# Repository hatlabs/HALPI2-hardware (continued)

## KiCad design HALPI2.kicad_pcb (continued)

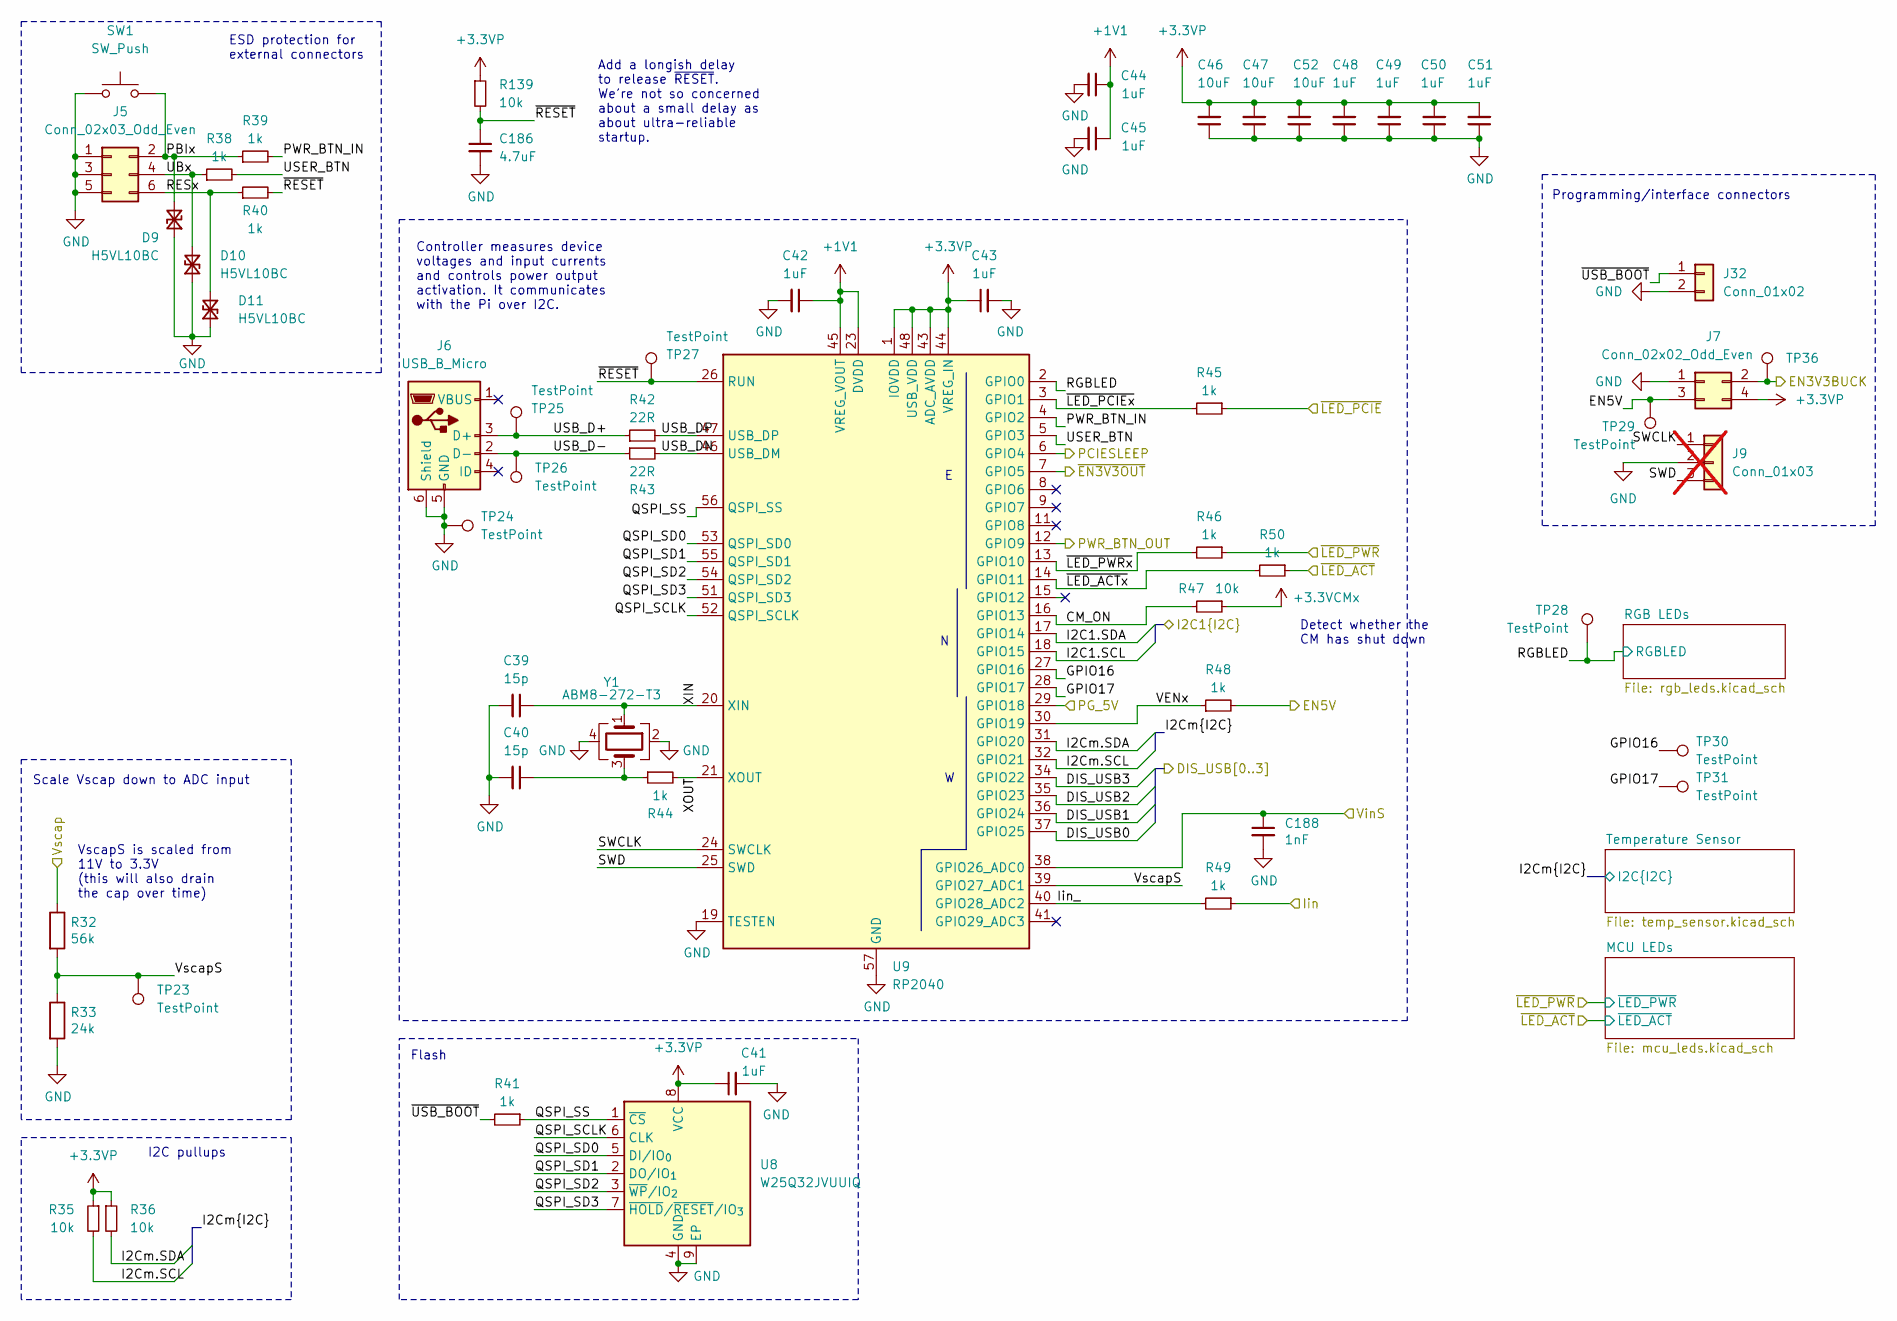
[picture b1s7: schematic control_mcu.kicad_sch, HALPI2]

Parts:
C39, C40: 15p; C_0402_1005Metric; LCSC C1548
C41, C42, C43, C44, C45, C48, C49, C50, C51: 1uF; C_0402_1005Metric; LCSC C52923
C46, C47, C52: 10uF; C_0603_1608Metric; LCSC C19702
C186: 4.7uF; C_0603_1608Metric; LCSC C19666
C188: 1nF; C_0402_1005Metric; LCSC C1523
D9, D10, D11: H5VL10BC; D_0402_1005Metric; LCSC C20615784
J5: Conn_02x03_Odd_Even; PinHeader_2x03_P2.54mm_Vertical_SMD; LCSC C3294461
J6: USB_B_Micro; MICRO-USB-SMD_920-154A2021Y10109; LCSC C399946
J7: Conn_02x02_Odd_Even; PinHeader_2x02_P2.54mm_Vertical_SMD; LCSC C919361
J9: Conn_01x03; PinHeader_1x03_P2.54mm_Vertical; not fitted
J32: Conn_01x02; PinHeader_1x02_P2.54mm_Vertical; LCSC C492401
R32: 56k; R_0402_1005Metric; LCSC C25796
R33: 24k; R_0402_1005Metric; LCSC C25769
R35, R36, R47: 10k; R_0402_1005Metric; LCSC C25744
R38, R39, R40, R41, R44, R45, R46, R48, R49, R50: 1k; R_0402_1005Metric; LCSC C11702
R42, R43: 22R; R_0402_1005Metric; LCSC C25092
R139: 10k; R_0603_1608Metric; LCSC C25804
SW1: SW_Push; SW_SPST_TL3342; LCSC C318887
TP23, TP24, TP25, TP26, TP27, TP28, TP29, TP30, TP31, TP36: TestPoint; TestPoint_Pad_D1.0mm
U8: W25Q32JVUUIQ; WSON-8-1EP_6x5mm_P1.27mm_EP3.4x4.3mm; LCSC C571260
U9: RP2040; QFN-56-1EP_7x7mm_P0.4mm_EP3.2x3.2mm; LCSC C2040
Y1: ABM8-272-T3; Crystal_SMD_3225-4Pin_3.2x2.5mm; LCSC C20625731

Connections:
+1V1: C42.1, C44.1, C45.1, U9.23 (DVDD), U9.45 (VREG_VOUT), U9.50 (DVDD)
+3.3VCMx: R47.1; also elsewhere on the board
+3.3VP: C41.1, C43.1, C46.2, C47.2, C48.2, C49.2, C50.2, C51.2, C52.2, J7.4, R35.1, R36.1, R139.1, U8.8 (VCC), U9.1 (IOVDD), U9.10 (IOVDD), U9.22 (IOVDD), U9.33 (IOVDD), U9.42 (IOVDD), U9.43 (ADC_AVDD), U9.44 (VREG_IN), U9.48 (USB_VDD), U9.49 (IOVDD); also elsewhere on the board
/Controller/CM_ON: R47.2, U9.16 (GPIO13)
/Controller/GPIO16: TP30.1 (1_1), U9.27 (GPIO16)
/Controller/GPIO17: TP31.1 (1_1), U9.28 (GPIO17)
/Controller/I2Cm.SCL: R35.2, U9.32 (GPIO21); also elsewhere on the board
/Controller/I2Cm.SDA: R36.2, U9.31 (GPIO20); also elsewhere on the board
/Controller/Iin_: R49.2, U9.40 (GPIO28_ADC2)
/Controller/PBIx: D9.2 (A2), J5.2, R39.1, SW1.2
/Controller/PWR_BTN_IN: R39.2, U9.4 (GPIO2)
/Controller/QSPI_SCLK: U8.6 (CLK), U9.52 (QSPI_SCLK)
/Controller/QSPI_SD0: U8.5 (DI/IO_{0}), U9.53 (QSPI_SD0)
/Controller/QSPI_SD1: U8.2 (DO/IO_{1}), U9.55 (QSPI_SD1)
/Controller/QSPI_SD2: U8.3 (~WP/IO_{2}), U9.54 (QSPI_SD2)
/Controller/QSPI_SD3: U8.7 (~HOLD/~RESET/IO_{3}), U9.51 (QSPI_SD3)
/Controller/QSPI_SS: R41.1, U8.1 (~CS), U9.56 (QSPI_SS)
/Controller/RESx: D11.2 (A2), J5.6, R40.1
/Controller/RGBLED: TP28.1 (1_1), U9.2 (GPIO0); also elsewhere on the board
/Controller/SWCLK: J9.1, U9.24 (SWCLK)
/Controller/SWD: J9.3, U9.25 (SWD)
/Controller/UBx: D10.2 (A2), J5.4, R38.1
/Controller/USB_D+: J6.3 (D+), R42.1, TP25.1 (1_1)
/Controller/USB_D-: J6.2 (D-), R43.1, TP26.1 (1_1)
/Controller/USB_DN: R43.2, U9.46 (USB_DM)
/Controller/USB_DP: R42.2, U9.47 (USB_DP)
/Controller/USER_BTN: R38.2, U9.5 (GPIO3)
/Controller/VENx: R48.1, U9.30 (GPIO19)
/Controller/VscapS: R32.2, R33.1, TP23.1 (1_1), U9.39 (GPIO27_ADC1)
/Controller/XIN: C39.1, U9.20 (XIN), Y1.1
/Controller/XOUT: R44.2, U9.21 (XOUT)
/Controller/~LED_ACTx: R50.2, U9.14 (GPIO11)
/Controller/~LED_PCIEx: R45.2, U9.3 (GPIO1)
/Controller/~LED_PWRx: R46.2, U9.13 (GPIO10)
/Controller/~RESET: C186.1, R40.2, R139.2, TP27.1 (1_1), U9.26 (RUN)
/Controller/~USB_BOOT: J32.1, R41.2
/DIS_USB0: U9.37 (GPIO25); also elsewhere on the board
/DIS_USB1: U9.36 (GPIO24); also elsewhere on the board
/DIS_USB2: U9.35 (GPIO23); also elsewhere on the board
/DIS_USB3: U9.34 (GPIO22); also elsewhere on the board
/EN3V3BUCK: J7.2, TP36.1 (1_1); also elsewhere on the board
/EN5V: J7.3, R48.2, TP29.1 (1_1); also elsewhere on the board
/I2C1.SCL: U9.18 (GPIO15); also elsewhere on the board
/I2C1.SDA: U9.17 (GPIO14); also elsewhere on the board
/Iin: R49.1; also elsewhere on the board
/PCIESLEEP: U9.6 (GPIO4); also elsewhere on the board
/PG_5V: U9.29 (GPIO18); also elsewhere on the board
/PWR_BUTTON: U9.12 (GPIO9); also elsewhere on the board
/VinS: C188.1, U9.38 (GPIO26_ADC0); also elsewhere on the board
/Vscap: R32.1; also elsewhere on the board
/~EN3V3OUT: U9.7 (GPIO5); also elsewhere on the board
/~LED_ACT: R50.1; also elsewhere on the board
/~LED_PCIE: R45.1; also elsewhere on the board
/~LED_PWR: R46.1; also elsewhere on the board
GND: C39.2, C40.2, C41.2, C42.2, C43.2, C44.2, C45.2, C46.1, C47.1, C48.1, C49.1, C50.1, C51.1, C52.1, C186.2, C188.2, D9.1 (A1), D10.1 (A1), D11.1 (A1), J5.1, J5.3, J5.5, J6.5 (GND), J6.6 (Shield), J7.1, J9.2, J32.2, R33.2, SW1.1, TP24.1 (1_1), U8.4 (GND), U8.9 (EP), U9.19 (TESTEN), U9.57 (GND), Y1.2, Y1.4; also elsewhere on the board
unnamed: C40.1, R44.1, Y1.3

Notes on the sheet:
Programming/interface connectors
Scale Vscap down to ADC input
ESD protection for external connectors
Detect whether the CM has shut down
I2C pullups
Add a longish delay to release ~{RESET}. We're not so concerned about a small delay as about ultra-reliable startup.
Controller measures device voltages and input currents and controls power output activation. It communicates with the Pi over I2C.
Flash
VscapS is scaled from 11V to 3.3V (this will also drain the cap over time)

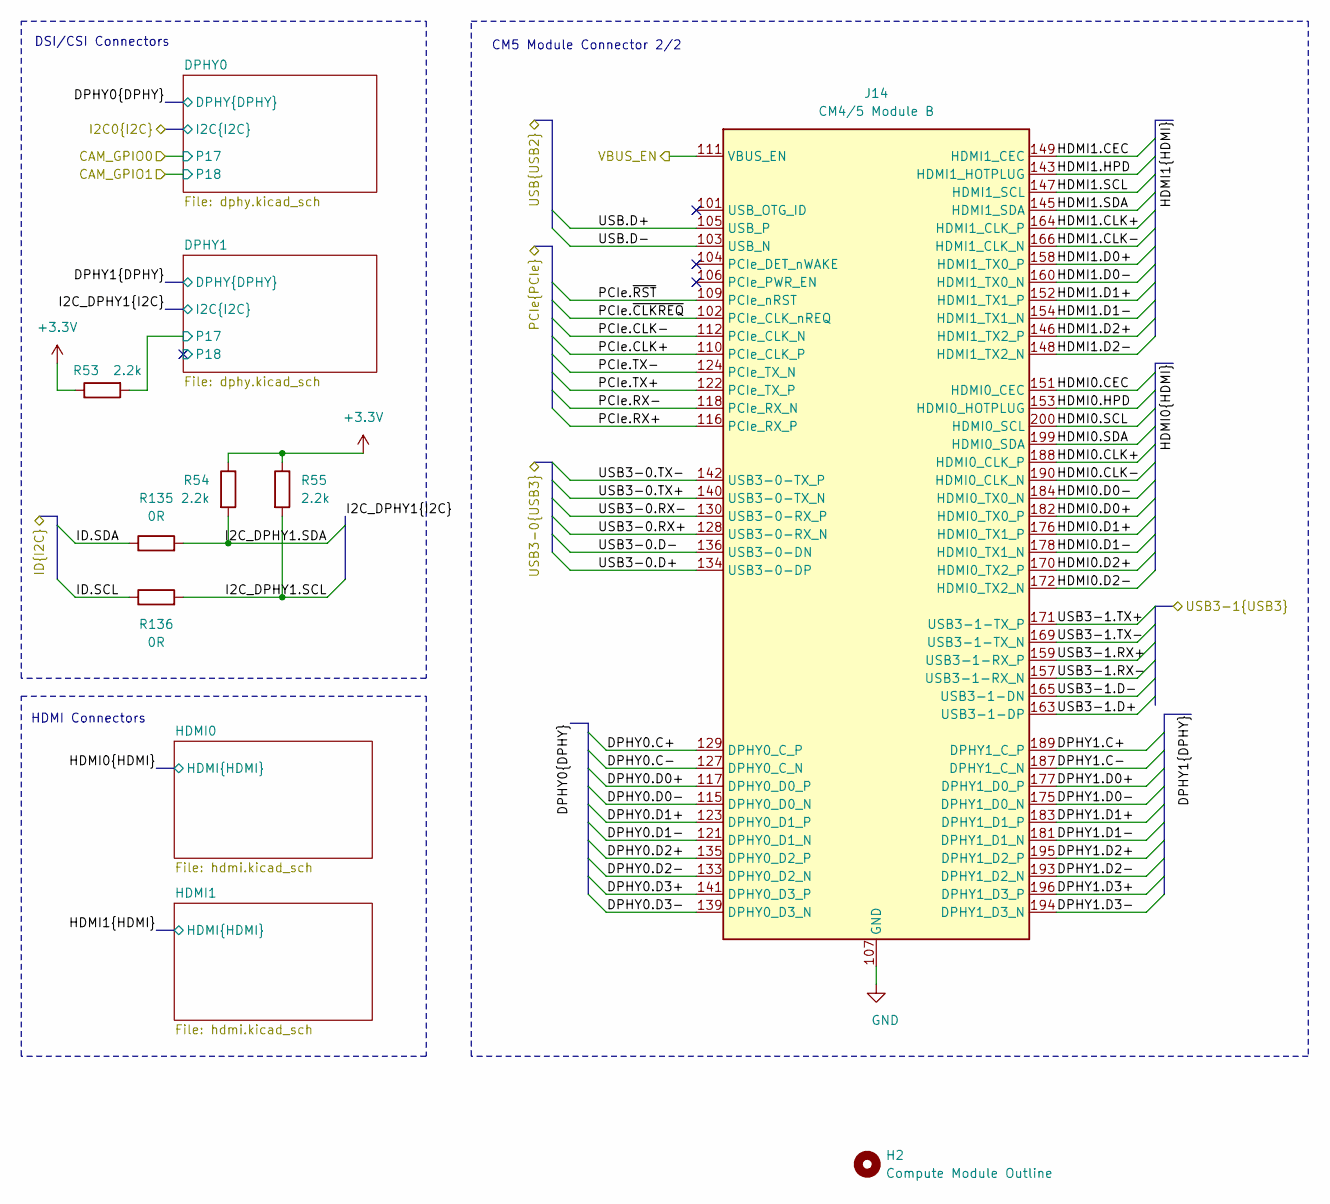
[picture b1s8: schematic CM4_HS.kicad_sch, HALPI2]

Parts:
H2: Compute Module Outline; RaspberryPi-CM4-Layout
J14: CM4/5 Module B; Hirose_DF40_DF40C-100DS-0.4V_2x50+100_P0.40mm_Vertical; LCSC C424649
R53, R54, R55: 2.2k; R_0402_1005Metric; LCSC C25879
R135, R136: 0R; R_0603_1608Metric_Pad0.98x0.95mm_HandSolder; LCSC C21189

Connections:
+3.3V: R53.1, R54.1, R55.1; also elsewhere on the board
/CM4 GPIO/ID.SCL: R136.1; also elsewhere on the board
/CM4 GPIO/ID.SDA: R135.1; also elsewhere on the board
/CM4 Highspeed/DPHY0.C+: J14.129 (DPHY0_C_P); also elsewhere on the board
/CM4 Highspeed/DPHY0.C-: J14.127 (DPHY0_C_N); also elsewhere on the board
/CM4 Highspeed/DPHY0.D0+: J14.117 (DPHY0_D0_P); also elsewhere on the board
/CM4 Highspeed/DPHY0.D0-: J14.115 (DPHY0_D0_N); also elsewhere on the board
/CM4 Highspeed/DPHY0.D1+: J14.123 (DPHY0_D1_P); also elsewhere on the board
/CM4 Highspeed/DPHY0.D1-: J14.121 (DPHY0_D1_N); also elsewhere on the board
/CM4 Highspeed/DPHY0.D2+: J14.135 (DPHY0_D2_P); also elsewhere on the board
/CM4 Highspeed/DPHY0.D2-: J14.133 (DPHY0_D2_N); also elsewhere on the board
/CM4 Highspeed/DPHY0.D3+: J14.141 (DPHY0_D3_P); also elsewhere on the board
/CM4 Highspeed/DPHY0.D3-: J14.139 (DPHY0_D3_N); also elsewhere on the board
/CM4 Highspeed/DPHY1.C+: J14.189 (DPHY1_C_P); also elsewhere on the board
/CM4 Highspeed/DPHY1.C-: J14.187 (DPHY1_C_N); also elsewhere on the board
/CM4 Highspeed/DPHY1.D0+: J14.177 (DPHY1_D0_P); also elsewhere on the board
/CM4 Highspeed/DPHY1.D0-: J14.175 (DPHY1_D0_N); also elsewhere on the board
/CM4 Highspeed/DPHY1.D1+: J14.183 (DPHY1_D1_P); also elsewhere on the board
/CM4 Highspeed/DPHY1.D1-: J14.181 (DPHY1_D1_N); also elsewhere on the board
/CM4 Highspeed/DPHY1.D2+: J14.195 (DPHY1_D2_P); also elsewhere on the board
/CM4 Highspeed/DPHY1.D2-: J14.193 (DPHY1_D2_N); also elsewhere on the board
/CM4 Highspeed/DPHY1.D3+: J14.196 (DPHY1_D3_P); also elsewhere on the board
/CM4 Highspeed/DPHY1.D3-: J14.194 (DPHY1_D3_N); also elsewhere on the board
/CM4 Highspeed/DPHY1/P17: R53.2; also elsewhere on the board
/CM4 Highspeed/HDMI0.CEC: J14.151 (HDMI0_CEC); also elsewhere on the board
/CM4 Highspeed/HDMI0.CLK+: J14.188 (HDMI0_CLK_P); also elsewhere on the board
/CM4 Highspeed/HDMI0.CLK-: J14.190 (HDMI0_CLK_N); also elsewhere on the board
/CM4 Highspeed/HDMI0.D0+: J14.182 (HDMI0_TX0_P); also elsewhere on the board
/CM4 Highspeed/HDMI0.D0-: J14.184 (HDMI0_TX0_N); also elsewhere on the board
/CM4 Highspeed/HDMI0.D1+: J14.176 (HDMI0_TX1_P); also elsewhere on the board
/CM4 Highspeed/HDMI0.D1-: J14.178 (HDMI0_TX1_N); also elsewhere on the board
/CM4 Highspeed/HDMI0.D2+: J14.170 (HDMI0_TX2_P); also elsewhere on the board
/CM4 Highspeed/HDMI0.D2-: J14.172 (HDMI0_TX2_N); also elsewhere on the board
/CM4 Highspeed/HDMI0.HPD: J14.153 (HDMI0_HOTPLUG); also elsewhere on the board
/CM4 Highspeed/HDMI0.SCL: J14.200 (HDMI0_SCL); also elsewhere on the board
/CM4 Highspeed/HDMI0.SDA: J14.199 (HDMI0_SDA); also elsewhere on the board
/CM4 Highspeed/HDMI1.CEC: J14.149 (HDMI1_CEC); also elsewhere on the board
/CM4 Highspeed/HDMI1.CLK+: J14.164 (HDMI1_CLK_P); also elsewhere on the board
/CM4 Highspeed/HDMI1.CLK-: J14.166 (HDMI1_CLK_N); also elsewhere on the board
/CM4 Highspeed/HDMI1.D0+: J14.158 (HDMI1_TX0_P); also elsewhere on the board
/CM4 Highspeed/HDMI1.D0-: J14.160 (HDMI1_TX0_N); also elsewhere on the board
/CM4 Highspeed/HDMI1.D1+: J14.152 (HDMI1_TX1_P); also elsewhere on the board
/CM4 Highspeed/HDMI1.D1-: J14.154 (HDMI1_TX1_N); also elsewhere on the board
/CM4 Highspeed/HDMI1.D2+: J14.146 (HDMI1_TX2_P); also elsewhere on the board
/CM4 Highspeed/HDMI1.D2-: J14.148 (HDMI1_TX2_N); also elsewhere on the board
/CM4 Highspeed/HDMI1.HPD: J14.143 (HDMI1_HOTPLUG); also elsewhere on the board
/CM4 Highspeed/HDMI1.SCL: J14.147 (HDMI1_SCL); also elsewhere on the board
/CM4 Highspeed/HDMI1.SDA: J14.145 (HDMI1_SDA); also elsewhere on the board
/CM4 Highspeed/I2C_DPHY1.SCL: R55.2, R136.2; also elsewhere on the board
/CM4 Highspeed/I2C_DPHY1.SDA: R54.2, R135.2; also elsewhere on the board
/PCIe.CLK+: J14.110 (PCIe_CLK_P); also elsewhere on the board
/PCIe.CLK-: J14.112 (PCIe_CLK_N); also elsewhere on the board
/PCIe.RX+: J14.116 (PCIe_RX_P); also elsewhere on the board
/PCIe.RX-: J14.118 (PCIe_RX_N); also elsewhere on the board
/PCIe.TX+: J14.122 (PCIe_TX_P); also elsewhere on the board
/PCIe.TX-: J14.124 (PCIe_TX_N); also elsewhere on the board
/PCIe.~CLKREQ: J14.102 (PCIe_CLK_nREQ); also elsewhere on the board
/PCIe.~RST: J14.109 (PCIe_nRST); also elsewhere on the board
/USB3-0.D+: J14.134 (USB3-0-DP); also elsewhere on the board
/USB3-0.D-: J14.136 (USB3-0-DN); also elsewhere on the board
/USB3-0.RX+: J14.128 (USB3-0-RX_N); also elsewhere on the board
/USB3-0.RX-: J14.130 (USB3-0-RX_P); also elsewhere on the board
/USB3-0.TX+: J14.140 (USB3-0-TX_N); also elsewhere on the board
/USB3-0.TX-: J14.142 (USB3-0-TX_P); also elsewhere on the board
/USB3-1.D+: J14.163 (USB3-1-DP); also elsewhere on the board
/USB3-1.D-: J14.165 (USB3-1-DN); also elsewhere on the board
/USB3-1.RX+: J14.159 (USB3-1-RX_P); also elsewhere on the board
/USB3-1.RX-: J14.157 (USB3-1-RX_N); also elsewhere on the board
/USB3-1.TX+: J14.171 (USB3-1-TX_P); also elsewhere on the board
/USB3-1.TX-: J14.169 (USB3-1-TX_N); also elsewhere on the board
/USB.D+: J14.105 (USB_P); also elsewhere on the board
/USB.D-: J14.103 (USB_N); also elsewhere on the board
/VBUS_EN: J14.111 (VBUS_EN); also elsewhere on the board
GND: J14.107 (GND), J14.108 (GND), J14.113 (GND), J14.114 (GND), J14.119 (GND), J14.120 (GND), J14.125 (GND), J14.126 (GND), J14.131 (GND), J14.132 (GND), J14.137 (GND), J14.138 (GND), J14.144 (GND), J14.150 (GND), J14.155 (GND), J14.156 (GND), J14.161 (GND), J14.162 (GND), J14.167 (GND), J14.168 (GND), J14.173 (GND), J14.174 (GND), J14.179 (GND), J14.180 (GND), J14.185 (GND), J14.186 (GND), J14.191 (GND), J14.192 (GND), J14.197 (GND), J14.198 (GND); also elsewhere on the board

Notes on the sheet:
DSI/CSI Connectors
HDMI Connectors
CM5 Module Connector 2/2

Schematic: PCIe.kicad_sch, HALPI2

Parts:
C16, C133, C134, C135: 1uF; C_0402_1005Metric; LCSC C52923
C18: 100pF C0G; C_0603_1608Metric; LCSC C14858
C136, C137: 10uF; C_0805_2012Metric; LCSC C15850
C802: 22pF C0G; C_0603_1608Metric; LCSC C1653
D27: BLUE LED; LED_0603_1608Metric; LCSC C84266
H3, H4, H5, H6: SMTSO2515CTJ; LCSC C2915629
J25: Bus_M.2_Socket_M; M.2_M-Key_Socket; LCSC C2832351
R95: 1k; R_0402_1005Metric; LCSC C11702
R149: 1M; R_0402_1005Metric; LCSC C26083
R150: 330k; R_0603_1608Metric; LCSC C23137
TP94, TP95, TP96: TestPoint; TestPoint_Pad_D1.0mm
U4: 74LVC1GU04; SOT-353_SC-70-5; LCSC C485082
Y801: X1A000061000200; Crystal_SMD_2012-2Pin_2.0x1.2mm; LCSC C55208

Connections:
+3.3V: C16.1, C133.1, C134.1, C135.1, C136.1, C137.1, J25.2 (3.3V), J25.4 (3.3V), J25.12 (3.3V), J25.14 (3.3V), J25.16 (3.3V), J25.18 (3.3V), J25.70 (3.3V), J25.72 (3.3V), J25.74 (3.3V), R95.1, U4.5 (VCC); also elsewhere on the board
/PCIESLEEP: J25.38 (DEVSLP); also elsewhere on the board
/PCIe.CLK+: J25.55 (REFCLKp); also elsewhere on the board
/PCIe.CLK-: J25.53 (REFCLKn); also elsewhere on the board
/PCIe.RX+: J25.43 (PERp0/SATA-B-); also elsewhere on the board
/PCIe.RX-: J25.41 (PERn0/SATA-B+); also elsewhere on the board
/PCIe.TX+: J25.49 (PETp0/SATA-A+); also elsewhere on the board
/PCIe.TX-: J25.47 (PETn0/SATA-A-); also elsewhere on the board
/PCIe.~CLKREQ: J25.52 (~CLKREQ); also elsewhere on the board
/PCIe.~RST: J25.50 (~PERST); also elsewhere on the board
/PCIe/OSCI: C802.2, R149.1, TP96.1 (1_1), U4.2, Y801.2
/PCIe/OSCO: C18.2, R149.2, R150.1, TP95.1 (1_1), Y801.1
/PCIe/SUSCLK: J25.68 (SUSCLK), R150.2, TP94.1 (1_1), U4.4
/~LED_PCIE: D27.1 (K), J25.10 (DAS/~DSS/~LED1); also elsewhere on the board
GND: C16.2, C18.1, C133.2, C134.2, C135.2, C136.2, C137.2, C802.1, H3.1 (1_1), H4.1 (1_1), H5.1 (1_1), H6.1 (1_1), J25.1 (GND), J25.3 (GND), J25.9 (GND), J25.15 (GND), J25.21 (GND), J25.27 (GND), J25.33 (GND), J25.39 (GND), J25.45 (GND), J25.51 (GND), J25.57 (GND), J25.71 (GND), J25.73 (GND), J25.75 (GND), J25.MP (GND), U4.3 (GND); also elsewhere on the board
unnamed: D27.2 (A), R95.2

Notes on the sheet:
PCIe allows diff pair polarity reversal for data lanes.
Temporary fix: ensure the oscillator starts even with a fast 74LVC inverter.

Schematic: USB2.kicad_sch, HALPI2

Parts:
J27: USB_C_Receptacle_USB2.0; USB_TYPE-C_SHOU-HAN_16PLT-H6.8; LCSC C5187468
R97: 2.7k; R_0603_1608Metric; LCSC C13167
R98, R99: 5.1k; R_0402_1005Metric; LCSC C25905
U43: RCLAMP0524P; Diodes_UDFN-10_1.0x2.5mm_P0.5mm; LCSC C907837

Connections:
/USB 2.0 Peripheral Interface/CC1: J27.A5 (CC1), R98.2
/USB 2.0 Peripheral Interface/CC2: J27.B5 (CC2), R99.2
/USB 2.0 Peripheral Interface/VBUS: J27.A4 (VBUS), J27.A9 (VBUS), J27.B4 (VBUS), J27.B9 (VBUS), R97.2, U43.4, U43.7
/USB.D+: J27.A6 (D+), J27.B6 (D+), U43.2, U43.9; also elsewhere on the board
/USB.D-: J27.A7 (D-), J27.B7 (D-), U43.1, U43.10; also elsewhere on the board
GND: J27.A1 (GND), J27.A12 (GND), J27.B1 (GND), J27.B12 (GND), J27.S1 (SHIELD), R97.1, R98.1, R99.1, U43.3 (VSS), U43.8 (VSS); also elsewhere on the board
unnamed: U43.5, U43.6

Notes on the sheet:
USB-C Receptacle and ESD protection USB 2.0 Peripheral operation only

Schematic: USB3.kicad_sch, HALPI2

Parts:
Q7: MMBT5551; SOT-23; LCSC C2145
R64, R65: 10k; R_0402_1005Metric; LCSC C25744

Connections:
+3.3V: R65.1; also elsewhere on the board
/USB3/B: Q7.1 (B), R64.2
/USB3/~EN: Q7.3 (C), R65.2; also elsewhere on the board
/VBUS_EN: R64.1; also elsewhere on the board
GND: Q7.2 (E); also elsewhere on the board

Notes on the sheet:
Invert EN for USB3-0

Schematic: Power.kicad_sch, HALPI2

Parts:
J1: Conn_01x02; PhoenixContact_MCV_1,5_2-G-3.81_1x02_P3.81mm_Vertical; LCSC C8396

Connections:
/Power/Vin: J1.2; also elsewhere on the board
GNDPWR: J1.1; also elsewhere on the board

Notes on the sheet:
10-38V
10-100V
3.3V / 3A
4 * 2.7V supercaps and balancing circuit
5-10.3V 0-5V at startup
5.1V / 4A Pi CM module USB outputs
Fuse TVS Reverse polarity prot. Reverse current prot. EMI filtering
Drop input to 10.0V Limit input current to 0.8A

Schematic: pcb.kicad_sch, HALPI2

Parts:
H7, H8, H9, H10, H11, H12: MountingHole; MountingHole_4.3x6.2mm_M4_Pad_Via
H13, H14, H15, H16: MountingHole; MountingHole_4.3mm_M4_Outline
H17, H18, H19, H20, H21: SMTSO2515CTJ; LCSC C2915629
H22, H23, H24, H25: SMTSO2530CTJ; SMTSO2515CTJ; LCSC C2915631
IMG1: HL logo; Hat_Labs_logo_20mm
IMG2: OSHW logo; OSHW-Logo2_14.6x12mm_SilkScreen
IMG3: WEEE logo; WEEE-Logo_8.4x12mm_SilkScreen
IMG4: CE logo; CE-Logo_11.2x8mm_SilkScreen
IMG5: Enclosure outline; AB-FA-12-1B_intersection
J30, J31, J33, J34: Conn_01x03; PinHeader_1x03_P2.54mm_Vertical
TP71, TP72, TP73, TP74, TP75, TP76, TP77, TP78, TP79, TP80, TP81, TP82, TP83, TP84, TP85: TestPoint; TestPoint_Pad_1.5x1.5mm

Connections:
+3.3V: J30.2, J31.2, J33.2, J34.2; also elsewhere on the board
+5V: J30.3, J31.3, J33.3, J34.3; also elsewhere on the board
GND: H7.1 (1_1), H8.1 (1_1), H9.1 (1_1), H10.1 (1_1), H11.1 (1_1), H12.1 (1_1), H17.1 (1_1), J30.1, J31.1, J33.1, J34.1, TP71.1 (1_1), TP72.1 (1_1), TP73.1 (1_1), TP74.1 (1_1), TP75.1 (1_1), TP76.1 (1_1), TP77.1 (1_1), TP78.1 (1_1), TP79.1 (1_1), TP80.1 (1_1), TP81.1 (1_1), TP82.1 (1_1), TP83.1 (1_1), TP84.1 (1_1), TP85.1 (1_1); also elsewhere on the board

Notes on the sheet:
Mounting nuts for HAT corners
Mounting nut for PoE HAT
Board end mounting holes
Board corner mounting holes
Mounting nuts for CM5 corners

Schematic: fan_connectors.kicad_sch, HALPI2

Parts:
C61, C62: 1uF; C_0402_1005Metric; LCSC C52923
C63, C64: 10uF; C_0603_1608Metric; LCSC C19702
J12, J13: HC-1.0-4PLT; JST_SH_HCTL_HC-1.0-4PLT_1x04-1MP_P1.00mm_Vertical; LCSC C2845372

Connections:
+5V: C61.1, C62.1, C63.1, C64.1, J12.1, J13.1; also elsewhere on the board
/CM4 GPIO/CM5_FAN_PWM: J12.2, J13.2; also elsewhere on the board
/CM4 GPIO/FAN_TACHO: J12.4, J13.4; also elsewhere on the board
GND: C61.2, C62.2, C63.2, C64.2, J12.3, J12.MP (MountPin), J13.3, J13.MP (MountPin); also elsewhere on the board

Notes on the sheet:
FAN connectors
Provide fan connectors on both top and bottom side of the board

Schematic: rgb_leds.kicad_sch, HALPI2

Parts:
C55: 10uF; C_0603_1608Metric; LCSC C19702
C56, C57, C58, C59, C60: 1uF; C_0402_1005Metric; LCSC C52923
D14, D15: 1N5819WS; D_SOD-323; LCSC C191023
LED1, LED2, LED3, LED4, LED5: SK6805SIDE-G-003; LED-SMD_4P-L3.5-W1.55_SK6805SIDE-G; LCSC C31452139
TP34: TestPoint; TestPoint_Pad_D1.0mm

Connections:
+3.3VP: D14.2 (A); also elsewhere on the board
+5V: D15.2 (A); also elsewhere on the board
/Controller/RGB LEDs/DIN2: LED1.1 (DOUT), LED2.4 (DIN)
/Controller/RGB LEDs/DIN3: LED2.1 (DOUT), LED3.4 (DIN)
/Controller/RGB LEDs/DIN4: LED3.1 (DOUT), LED4.4 (DIN)
/Controller/RGB LEDs/DIN5: LED4.1 (DOUT), LED5.4 (DIN)
/Controller/RGB LEDs/DOUT: LED5.1 (DOUT), TP34.1 (1_1)
/Controller/RGB LEDs/LED_5V: C55.1, C56.1, C57.1, C58.1, C59.1, C60.1, D14.1 (K), D15.1 (K), LED1.3 (VCC), LED2.3 (VCC), LED3.3 (VCC), LED4.3 (VCC), LED5.3 (VCC)
/Controller/RGBLED: LED1.4 (DIN); also elsewhere on the board
GND: C55.2, C56.2, C57.2, C58.2, C59.2, C60.2, LED1.2 (GND), LED2.2 (GND), LED3.2 (GND), LED4.2 (GND), LED5.2 (GND); also elsewhere on the board

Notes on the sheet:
RGB LEDs

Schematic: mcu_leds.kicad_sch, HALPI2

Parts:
C185: 1uF; C_0402_1005Metric; LCSC C52923
D39, D41, D43: RED LED; LED_0603_1608Metric; LCSC C2286
D40: GREEN LED; LED_0603_1608Metric; LCSC C965804
R131: 100k; R_0402_1005Metric; LCSC C25741
R132, R134: 2.7k; R_0603_1608Metric; LCSC C13167
R133: 2k; R_0402_1005Metric; LCSC C4109
R140: 6.2k; R_0603_1608Metric; LCSC C4260
U3: 74LVC1GU04; SOT-353_SC-70-5; LCSC C485082

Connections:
+3.3V: C185.1, R131.1, R133.1, R134.1, U3.5 (VCC); also elsewhere on the board
+5V: R140.1; also elsewhere on the board
/~LED_ACT: D40.1 (K); also elsewhere on the board
/~LED_PWR: R131.2, U3.2; also elsewhere on the board
GND: C185.2, D39.1 (K), D41.1 (K), D43.1 (K), U3.3 (GND); also elsewhere on the board
unnamed: D39.2 (A), R132.2
unnamed: D40.2 (A), R133.2
unnamed: D41.2 (A), R134.2
unnamed: D43.2 (A), R140.2
unnamed: R132.1, U3.4

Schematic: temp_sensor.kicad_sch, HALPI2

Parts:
C184: 1uF; C_0402_1005Metric; LCSC C52923
U53: TMP112AIDRL; SOT-563; LCSC C28927

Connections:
+3.3V: C184.1, U53.5 (V+); also elsewhere on the board
/Controller/I2Cm.SCL: U53.1 (SCL), U53.4 (ADD0); also elsewhere on the board
/Controller/I2Cm.SDA: U53.6 (SDA); also elsewhere on the board
GND: C184.2, U53.2 (GND); also elsewhere on the board

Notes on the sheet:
I2C address 0x4b

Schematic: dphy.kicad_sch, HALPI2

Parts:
J15: FFC-22p-P0.5mm; FPC-SMD_22P-P0.50_XUNPU_FPC-05F-22PH20_REV_Horizontal; LCSC C2856804
U11, U12, U13, U14: RCLAMP0524P; Diodes_UDFN-10_1.0x2.5mm_P0.5mm; LCSC C907837

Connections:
+3.3V: J15.22, U14.4, U14.7; also elsewhere on the board
/CM4 GPIO/CAM_GPIO0: J15.17, U13.4, U13.7; also elsewhere on the board
/CM4 GPIO/CAM_GPIO1: J15.18, U13.5, U13.6; also elsewhere on the board
/CM4 Highspeed/DPHY0.C+: J15.9, U12.2, U12.9; also elsewhere on the board
/CM4 Highspeed/DPHY0.C-: J15.8, U12.1, U12.10; also elsewhere on the board
/CM4 Highspeed/DPHY0.D0+: J15.3, U11.2, U11.9; also elsewhere on the board
/CM4 Highspeed/DPHY0.D0-: J15.2, U11.1, U11.10; also elsewhere on the board
/CM4 Highspeed/DPHY0.D1+: J15.6, U11.5, U11.6; also elsewhere on the board
/CM4 Highspeed/DPHY0.D1-: J15.5, U11.4, U11.7; also elsewhere on the board
/CM4 Highspeed/DPHY0.D2+: J15.12, U12.5, U12.6; also elsewhere on the board
/CM4 Highspeed/DPHY0.D2-: J15.11, U12.4, U12.7; also elsewhere on the board
/CM4 Highspeed/DPHY0.D3+: J15.15, U13.2, U13.9; also elsewhere on the board
/CM4 Highspeed/DPHY0.D3-: J15.14, U13.1, U13.10; also elsewhere on the board
/I2C0.SCL: J15.20, U14.1, U14.10; also elsewhere on the board
/I2C0.SDA: J15.21, U14.2, U14.9; also elsewhere on the board
GND: J15.1, J15.4, J15.7, J15.10, J15.13, J15.16, J15.19, J15.MP (MountPin), U11.3 (VSS), U11.8 (VSS), U12.3 (VSS), U12.8 (VSS), U13.3 (VSS), U13.8 (VSS), U14.3 (VSS), U14.8 (VSS); also elsewhere on the board
unnamed: U14.5, U14.6

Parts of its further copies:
J16: FFC-22p-P0.5mm; FPC-SMD_22P-P0.50_XUNPU_FPC-05F-22PH20_REV_Horizontal; LCSC C2856804
U15, U16, U17, U18: RCLAMP0524P; Diodes_UDFN-10_1.0x2.5mm_P0.5mm; LCSC C907837

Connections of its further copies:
+3.3V: J16.22, U18.4, U18.7; also elsewhere on the board
/CM4 Highspeed/DPHY1.C+: J16.9, U16.2, U16.9; also elsewhere on the board
/CM4 Highspeed/DPHY1.C-: J16.8, U16.1, U16.10; also elsewhere on the board
/CM4 Highspeed/DPHY1.D0+: J16.3, U15.2, U15.9; also elsewhere on the board
/CM4 Highspeed/DPHY1.D0-: J16.2, U15.1, U15.10; also elsewhere on the board
/CM4 Highspeed/DPHY1.D1+: J16.6, U15.5, U15.6; also elsewhere on the board
/CM4 Highspeed/DPHY1.D1-: J16.5, U15.4, U15.7; also elsewhere on the board
/CM4 Highspeed/DPHY1.D2+: J16.12, U16.5, U16.6; also elsewhere on the board
/CM4 Highspeed/DPHY1.D2-: J16.11, U16.4, U16.7; also elsewhere on the board
/CM4 Highspeed/DPHY1.D3+: J16.15, U17.2, U17.9; also elsewhere on the board
/CM4 Highspeed/DPHY1.D3-: J16.14, U17.1, U17.10; also elsewhere on the board
/CM4 Highspeed/DPHY1/P17: J16.17, U17.4, U17.7; also elsewhere on the board
/CM4 Highspeed/DPHY1/P18: J16.18, U17.5, U17.6
/CM4 Highspeed/I2C_DPHY1.SCL: J16.20, U18.1, U18.10; also elsewhere on the board
/CM4 Highspeed/I2C_DPHY1.SDA: J16.21, U18.2, U18.9; also elsewhere on the board
GND: J16.1, J16.4, J16.7, J16.10, J16.13, J16.16, J16.19, J16.MP (MountPin), U15.3 (VSS), U15.8 (VSS), U16.3 (VSS), U16.8 (VSS), U17.3 (VSS), U17.8 (VSS), U18.3 (VSS), U18.8 (VSS); also elsewhere on the board
unnamed: U18.5, U18.6

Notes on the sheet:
DSI diff pair polarity MUST be maintained!

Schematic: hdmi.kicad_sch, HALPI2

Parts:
C65, C67: 10uF; C_0805_2012Metric; LCSC C15850
C66: 1uF; C_0402_1005Metric; LCSC C52923
D18: H5VL10BC; D_0402_1005Metric; LCSC C20615784
J17: FPC0.5-SMT-20P; FPC-SMD_20P-P0.50_XUNPU_FPC-05F-20PH20_Horizontal; LCSC C2856803
R56: 49.9k; R_0603_1608Metric; LCSC C23184
TP37: TestPoint; TestPoint_Pad_D1.0mm
U19: AP2553W6-7; SOT-23-6; LCSC C212302
U20, U21, U22: RCLAMP0524P; Diodes_UDFN-10_1.0x2.5mm_P0.5mm; LCSC C907837

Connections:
+5V: C65.1, C66.1, U19.1 (IN), U19.3 (EN); also elsewhere on the board
/CM4 Highspeed/HDMI0.CEC: J17.13, U20.5, U20.6; also elsewhere on the board
/CM4 Highspeed/HDMI0.CLK+: J17.10, U21.2, U21.9; also elsewhere on the board
/CM4 Highspeed/HDMI0.CLK-: J17.11, U21.1, U21.10; also elsewhere on the board
/CM4 Highspeed/HDMI0.D0+: J17.7, U21.5, U21.6; also elsewhere on the board
/CM4 Highspeed/HDMI0.D0-: J17.8, U21.4, U21.7; also elsewhere on the board
/CM4 Highspeed/HDMI0.D1+: J17.4, U22.2, U22.9; also elsewhere on the board
/CM4 Highspeed/HDMI0.D1-: J17.6, U22.1, U22.10; also elsewhere on the board
/CM4 Highspeed/HDMI0.D2+: J17.1, U22.5, U22.6; also elsewhere on the board
/CM4 Highspeed/HDMI0.D2-: J17.3, U22.4, U22.7; also elsewhere on the board
/CM4 Highspeed/HDMI0.HPD: J17.19, U20.1, U20.10; also elsewhere on the board
/CM4 Highspeed/HDMI0.SCL: J17.14, U20.4, U20.7; also elsewhere on the board
/CM4 Highspeed/HDMI0.SDA: J17.16, U20.2, U20.9; also elsewhere on the board
/CM4 Highspeed/HDMI0/+5V_HDMI: C67.1, D18.2 (A2), J17.17, TP37.1 (1_1), U19.6 (OUT)
/CM4 Highspeed/HDMI0/ILIM: R56.2, U19.5 (ILIM)
GND: C65.2, C66.2, C67.2, D18.1 (A1), J17.2, J17.5, J17.9, J17.12, J17.18, J17.20, J17.MP (MountPin), R56.1, U19.2 (GND), U20.3 (VSS), U20.8 (VSS), U21.3 (VSS), U21.8 (VSS), U22.3 (VSS), U22.8 (VSS); also elsewhere on the board

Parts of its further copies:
C68, C70: 10uF; C_0805_2012Metric; LCSC C15850
C69: 1uF; C_0402_1005Metric; LCSC C52923
D19: H5VL10BC; D_0402_1005Metric; LCSC C20615784
J18: FPC0.5-SMT-20P; FPC-SMD_20P-P0.50_XUNPU_FPC-05F-20PH20_Horizontal; LCSC C2856803
R57: 49.9k; R_0603_1608Metric; LCSC C23184
TP38: TestPoint; TestPoint_Pad_D1.0mm
U23: AP2553W6-7; SOT-23-6; LCSC C212302
U24, U25, U26: RCLAMP0524P; Diodes_UDFN-10_1.0x2.5mm_P0.5mm; LCSC C907837

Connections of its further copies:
+5V: C68.1, C69.1, U23.1 (IN), U23.3 (EN); also elsewhere on the board
/CM4 Highspeed/HDMI1.CEC: J18.13, U24.5, U24.6; also elsewhere on the board
/CM4 Highspeed/HDMI1.CLK+: J18.10, U25.2, U25.9; also elsewhere on the board
/CM4 Highspeed/HDMI1.CLK-: J18.11, U25.1, U25.10; also elsewhere on the board
/CM4 Highspeed/HDMI1.D0+: J18.7, U25.5, U25.6; also elsewhere on the board
/CM4 Highspeed/HDMI1.D0-: J18.8, U25.4, U25.7; also elsewhere on the board
/CM4 Highspeed/HDMI1.D1+: J18.4, U26.2, U26.9; also elsewhere on the board
/CM4 Highspeed/HDMI1.D1-: J18.6, U26.1, U26.10; also elsewhere on the board
/CM4 Highspeed/HDMI1.D2+: J18.1, U26.5, U26.6; also elsewhere on the board
/CM4 Highspeed/HDMI1.D2-: J18.3, U26.4, U26.7; also elsewhere on the board
/CM4 Highspeed/HDMI1.HPD: J18.19, U24.1, U24.10; also elsewhere on the board
/CM4 Highspeed/HDMI1.SCL: J18.14, U24.4, U24.7; also elsewhere on the board
/CM4 Highspeed/HDMI1.SDA: J18.16, U24.2, U24.9; also elsewhere on the board
/CM4 Highspeed/HDMI1/+5V_HDMI: C70.1, D19.2 (A2), J18.17, TP38.1 (1_1), U23.6 (OUT)
/CM4 Highspeed/HDMI1/ILIM: R57.2, U23.5 (ILIM)
GND: C68.2, C69.2, C70.2, D19.1 (A1), J18.2, J18.5, J18.9, J18.12, J18.18, J18.20, J18.MP (MountPin), R57.1, U23.2 (GND), U24.3 (VSS), U24.8 (VSS), U25.3 (VSS), U25.8 (VSS), U26.3 (VSS), U26.8 (VSS); also elsewhere on the board

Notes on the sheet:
P18
HDMI diff pair polarity MUST be maintained.
P17
P10
UTILITY
P11
D1 GND
P19
Current limiting
P12
P15
D0 GND
AUX GND
D2 GND
P16
P14
CLK GND
P13
